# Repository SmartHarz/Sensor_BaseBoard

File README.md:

# Bosch Sensortec BME688 Breadboard Adapter

A simplistic sensor base board for BME688 air quality sensor by Bosch Sensortec

The design allows for V<sub>CC</sub> and logic levels between 3V3 and 5V DC.

Due to the fact that the BME688 sensor features an LGA footprints with all pads below the sensor, manual soldering with a soldering iron is not possible for the sensor itself. All other parts can be soldered by hand, even though the 0402 components require a steady hand. Either way reflow soldering makes life a lot easier, if you keep the airflow low enough to not blow away your components. :wink:

The project folder [panel](/Sensor_BaseBoard/panel/) contains a panelized version as well

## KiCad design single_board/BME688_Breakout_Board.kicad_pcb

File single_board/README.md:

# Bosch Sensortec BMEx80 Breadboard Adapter

This folder contains the [KiCAD](https://www.kicad.org/) project for the single adapter.

## Schematic

PDF of the schematic is available [here](BME688_Breakout_Board_Schematic.pdf).

## Layout

As 4 layer boards nowadays are available at a similar price as 2 layer boards, I went for 4 layers, with dedicated GND and 3V3 planes in the middle.

A PDF of the layout is available [here](BME688_Breakout_Board_SingleLayers.pdf)(single page per layer) and [here](BME688_Breakout_Board_Condensed.pdf)(all layers condensed).

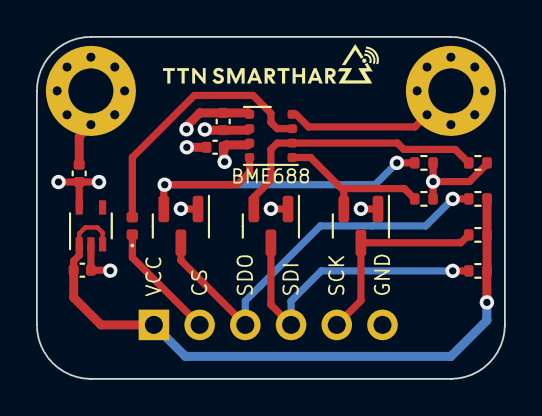
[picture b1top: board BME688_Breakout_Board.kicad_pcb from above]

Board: 4 copper layers, 26.0 x 19.0 mm, 19 parts (0 on the bottom side), 11 nets.

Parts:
C1, C2: 1u; C_0402_1005Metric
C3, C4: 100n; C_0402_1005Metric
D1: Diode; D_0402_1005Metric
H1, H2: MountingHole_Pad; MountingHole_2.5mm_Pad_Via
J1: External; PinHeader_1x06_P2.54mm_Vertical
Q1, Q2, Q3: BSS138; SOT-23
R1, R2, R3, R4, R5, R6: 4k7; R_0402_1005Metric
U1: BME688; Bosch_LGA-8_3x3mm_P0.8mm_ClockwisePinNumbering
U2: STLQ020C33R; SOT323-5L

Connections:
+3V3: C2.1, C3.1, C4.1, Q1.1 (G), Q2.1 (G), Q3.1 (G), R1.1, R3.1, R5.1, U1.6 (VDDIO), U1.8 (VDD), U2.5 (VOUT)
/+3.3V_CS: D1.2 (A), U1.2 (CSB)
/+3.3V_SCK: Q2.2 (S), R3.2, U1.4 (SCK)
/+3.3V_SDI: Q1.2 (S), R1.2, U1.3 (SDI)
/+3.3V_SDO: Q3.2 (S), R5.2, U1.5 (SDO)
/+5V_CS: D1.1 (K), J1.2
/+5V_SCK: J1.5, Q2.3 (D), R4.2
/+5V_SDI: J1.4, Q1.3 (D), R2.2
/+5V_SDO: J1.3, Q3.3 (D), R6.2
GND: C1.2, C2.2, C3.2, C4.2, H1.1, H2.1, J1.6, U1.1 (GND), U1.7 (GND), U2.2 (GND)
VCC: C1.1, J1.1, R2.1, R4.1, R6.1, U2.1 (VIN), U2.3 (EN)

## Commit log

2022-04-03 Added project libs
2022-05-21 Corrections
2022-05-21 Create LICENSE
2023-02-03 Update LICENSE
